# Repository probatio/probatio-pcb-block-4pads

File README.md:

# probatio-pcb-block-4pads
PCB designs of 4 pads with LEDs for probatio

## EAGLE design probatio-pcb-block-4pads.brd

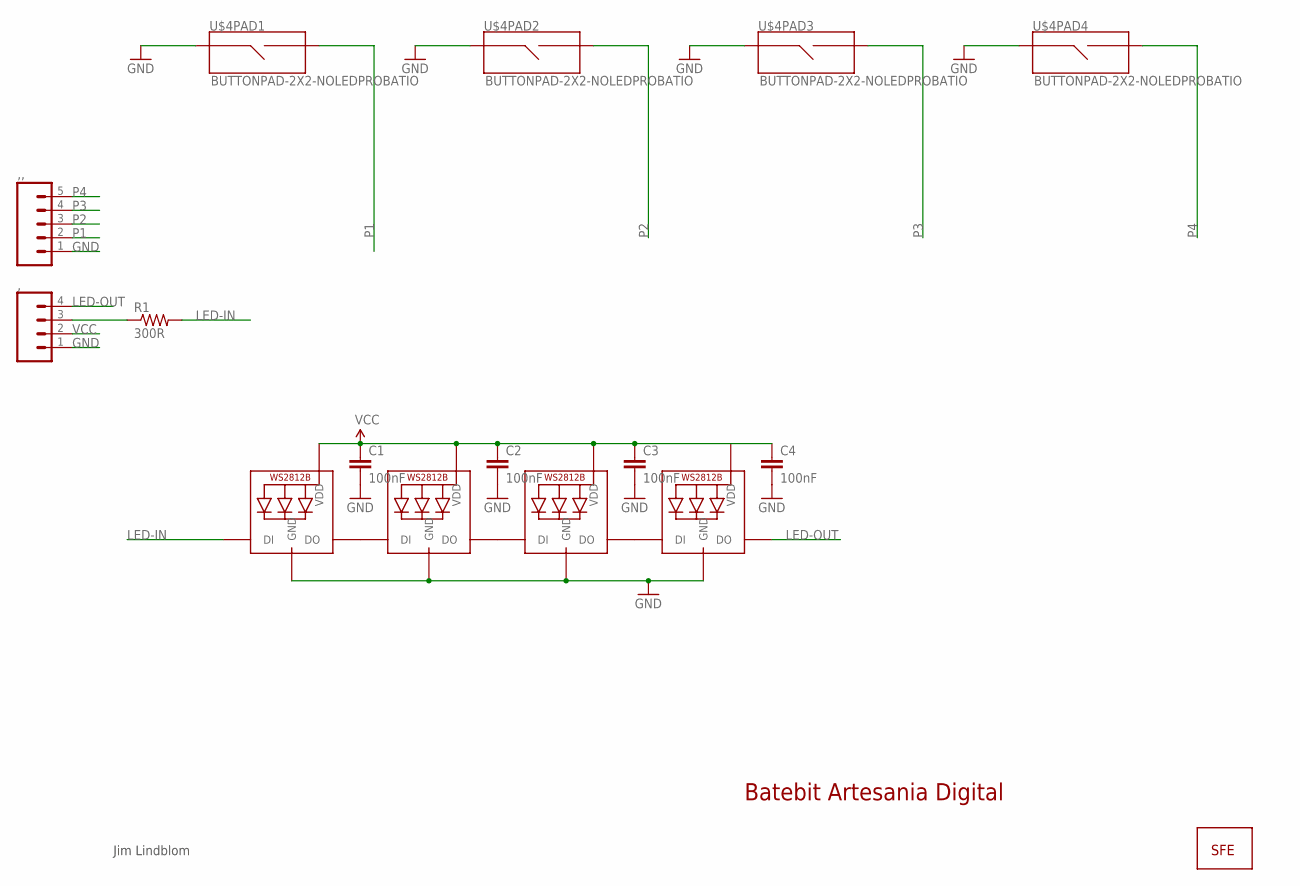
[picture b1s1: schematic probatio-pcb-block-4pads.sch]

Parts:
,: CONN_04PTH; 1X04
,,: M05PTH; 1X05
C1, C2, C3, C4: 100nF; 0805-CAP
LED1, LED2, LED3, LED4: WS2812B3535; LED3535
R1: 300R; AXIAL-0.4
U$1: LOGO-SFENEW; SFE-NEW-WEBLOGO
U$4: BUTTONPAD-2X2-NOLEDPROBATIO; BUTTONPAD-2X2-PROBATIO-NOLED

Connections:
GND: ,.1, ,,.1, C1.2, C2.2, C3.2, C4.2, LED1.4 (GND), LED2.4 (GND), LED3.4 (GND), LED4.4 (GND), U$4.SIG1, U$4.SIG3 (SIG1), U$4.SIG5 (SIG1), U$4.SIG7 (SIG1)
L: ,.3, R1.P$1 (1)
LED-IN: LED1.1 (DI), R1.P$2 (2)
LED-OUT: ,.4, LED4.3 (DO)
unnamed: LED1.3 (DO), LED2.1 (DI)
unnamed: LED2.3 (DO), LED3.1 (DI)
unnamed: LED3.3 (DO), LED4.1 (DI)
P1: ,,.2, U$4.SIG2
P2: ,,.3, U$4.SIG4 (SIG2)
P3: ,,.4, U$4.SIG6 (SIG2)
P4: ,,.5, U$4.SIG8 (SIG2)
VCC: ,.2, C1.1, C2.1, C3.1, C4.1, LED1.2 (VDD), LED2.2 (VDD), LED3.2 (VDD), LED4.2 (VDD)

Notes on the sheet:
Batebit Artesania Digital
Jim Lindblom

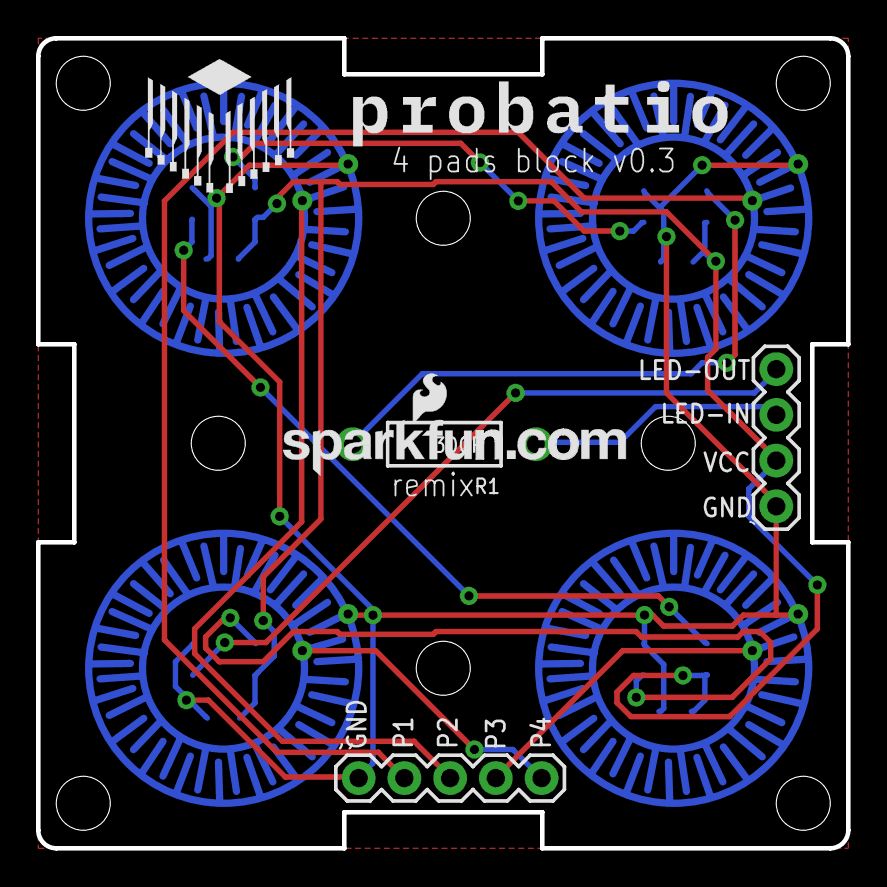
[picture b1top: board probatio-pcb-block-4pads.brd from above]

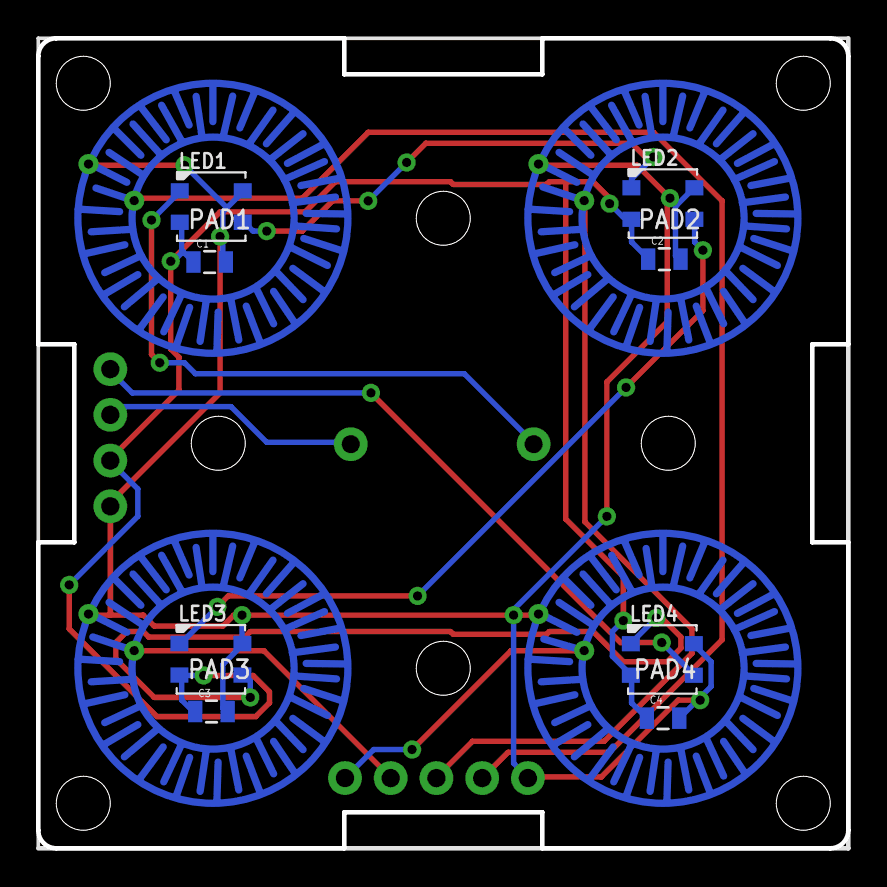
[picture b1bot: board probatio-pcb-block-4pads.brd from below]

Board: 2 copper layers, 45.0 x 45.0 mm, 14 parts (9 on the bottom side), 12 nets.

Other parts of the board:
U$3: PROBATIO

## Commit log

2021-02-25 v0.3 of the block
